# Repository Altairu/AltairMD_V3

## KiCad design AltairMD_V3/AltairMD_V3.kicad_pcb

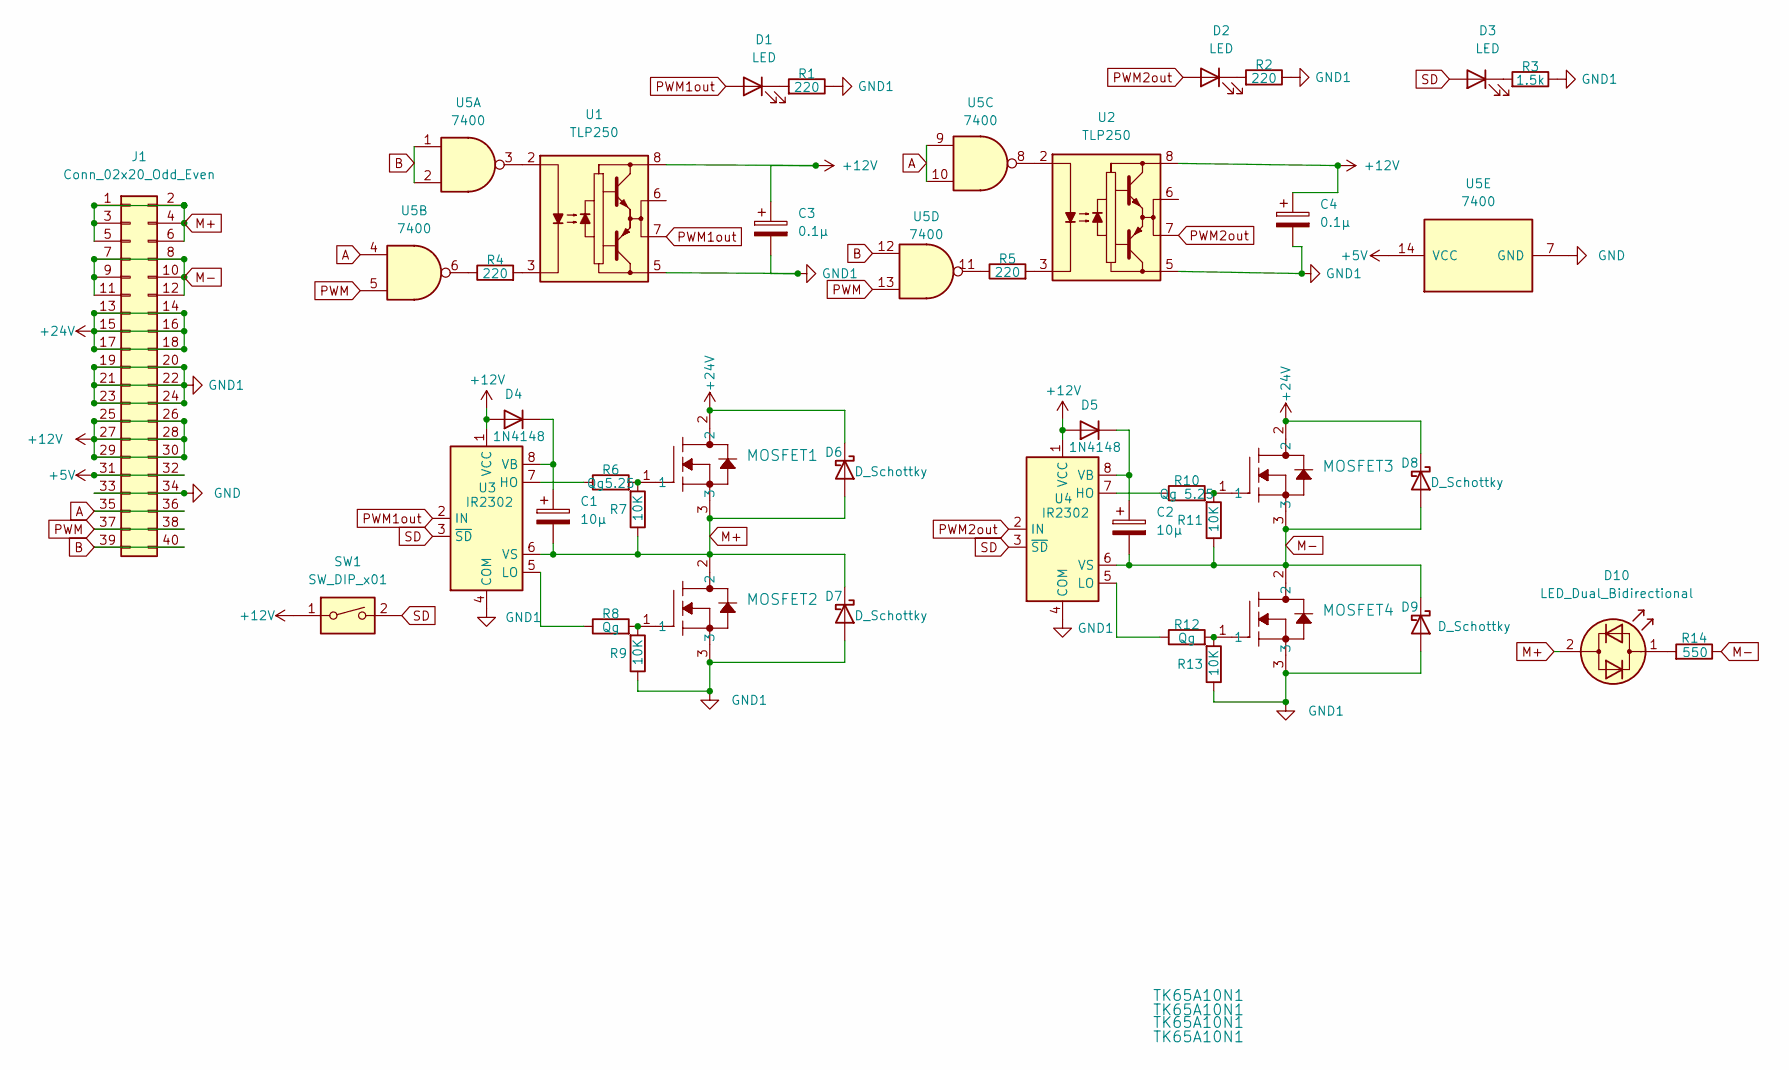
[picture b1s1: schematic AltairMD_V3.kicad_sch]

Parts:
C1, C2: 10μ; CP_Radial_D5.0mm_P2.00mm
C3, C4: 0.1μ; CP_Radial_D5.0mm_P2.00mm
D1, D2, D3: LED; LED_D3.0mm
D4, D5: 1N4148; D_DO-35_SOD27_P10.16mm_Horizontal
D6, D7, D8, D9: D_Schottky; D_DO-35_SOD27_P10.16mm_Horizontal
D10: LED_Dual_Bidirectional; LED_D3.0mm
J1: Conn_02x20_Odd_Even; PinHeader_2x20_P2.54mm_Horizontal
MOSFET1, MOSFET2, MOSFET3, MOSFET4: TK65A10N1; TO-220-3_Horizontal_TabDown
R1, R2, R4: 220; R_Axial_DIN0207_L6.3mm_D2.5mm_P10.16mm_Horizontal
R3: 1.5k; R_Axial_DIN0207_L6.3mm_D2.5mm_P10.16mm_Horizontal
R5: 220; R_Axial_DIN0207_L6.3mm_D2.5mm_P2.54mm_Vertical
R6: Qg5.25; R_Axial_DIN0207_L6.3mm_D2.5mm_P10.16mm_Horizontal
R7, R9, R11, R13: 10K; R_Axial_DIN0207_L6.3mm_D2.5mm_P10.16mm_Horizontal
R8, R12: Qg; R_Axial_DIN0207_L6.3mm_D2.5mm_P10.16mm_Horizontal
R10: Qg 5.25; R_Axial_DIN0207_L6.3mm_D2.5mm_P10.16mm_Horizontal
R14: 550; R_Axial_DIN0207_L6.3mm_D2.5mm_P10.16mm_Horizontal
SW1: SW_DIP_x01; PinHeader_1x02_P2.54mm_Vertical
U1, U2: TLP250; DIP-8_W7.62mm
U3, U4: IR2302; DIP-8_W7.62mm
U5: 7400; DIP-14_W7.62mm

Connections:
+5V: J1.31, J1.32, U5.14 (VCC)
+12V: C3.1, C4.1, D4.2 (A), D5.2 (A), J1.25, J1.26, J1.27, J1.28, J1.29, J1.30, SW1.1, U1.8 (VCC), U2.8 (VCC), U3.1 (VCC), U4.1 (VCC)
+24V: D6.1 (K), D8.1 (K), J1.13, J1.14, J1.15, J1.16, J1.17, J1.18, MOSFET1.2, MOSFET3.2
A: J1.35, J1.36, U5.4, U5.9, U5.10
B: J1.39, J1.40, U5.1, U5.2, U5.12
GND: J1.33, J1.34, U5.7 (GND)
GND1: C3.2, C4.2, D7.2 (A), D9.2 (A), J1.19, J1.20, J1.21, J1.22, J1.23, J1.24, MOSFET2.3, MOSFET4.3, R1.1, R2.1, R3.1, R9.1, R13.1, U1.5 (VEE), U2.5 (VEE), U3.4 (COM), U4.4 (COM)
M+: C1.2, D6.2 (A), D7.1 (K), D10.2 (AK), J1.1, J1.2, J1.3, J1.4, J1.5, J1.6, MOSFET1.3, MOSFET2.2, R7.1, U3.6 (VS)
M-: C2.2, D8.2 (A), D9.1 (K), J1.7, J1.8, J1.9, J1.10, J1.11, J1.12, MOSFET3.3, MOSFET4.2, R11.1, R14.1, U4.6 (VS)
unnamed: C1.1, D4.1 (K), U3.8 (VB)
unnamed: C2.1, D5.1 (K), U4.8 (VB)
unnamed: D1.1 (K), R1.2
unnamed: D2.1 (K), R2.2
unnamed: D3.1 (K), R3.2
unnamed: D10.1 (KA), R14.2
unnamed: MOSFET1.1, R6.2, R7.2
unnamed: MOSFET2.1, R8.2, R9.2
unnamed: MOSFET3.1, R10.2, R11.2
unnamed: MOSFET4.1, R12.2, R13.2
unnamed: R4.1, U5.6
unnamed: R4.2, U1.3 (C)
unnamed: R5.1, U5.11
unnamed: R5.2, U2.3 (C)
unnamed: R6.1, U3.7 (HO)
unnamed: R8.1, U3.5 (LO)
unnamed: R10.1, U4.7 (HO)
unnamed: R12.1, U4.5 (LO)
unnamed: U1.2 (A), U5.3
unnamed: U2.2 (A), U5.8
PWM: J1.37, J1.38, U5.5, U5.13
PWM1out: D1.2 (A), U1.7 (VO), U3.2 (IN)
PWM2out: D2.2 (A), U2.7 (VO), U4.2 (IN)
SD: D3.2 (A), SW1.2, U3.3 (~SD), U4.3 (~SD)

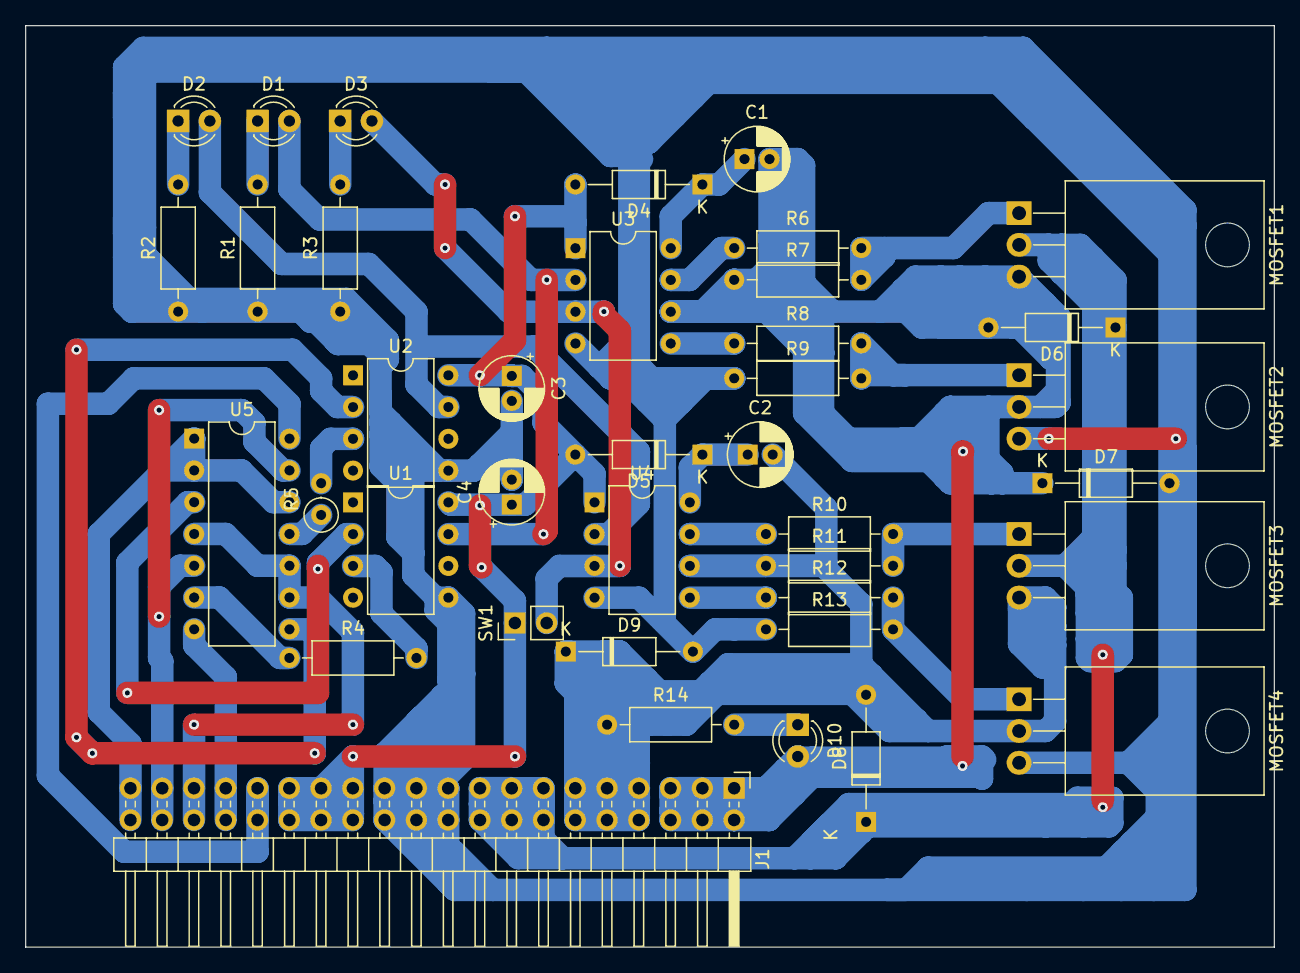
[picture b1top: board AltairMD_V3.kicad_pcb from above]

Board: 2 copper layers, 99.8 x 73.7 mm, 39 parts (0 on the bottom side), 33 nets.
